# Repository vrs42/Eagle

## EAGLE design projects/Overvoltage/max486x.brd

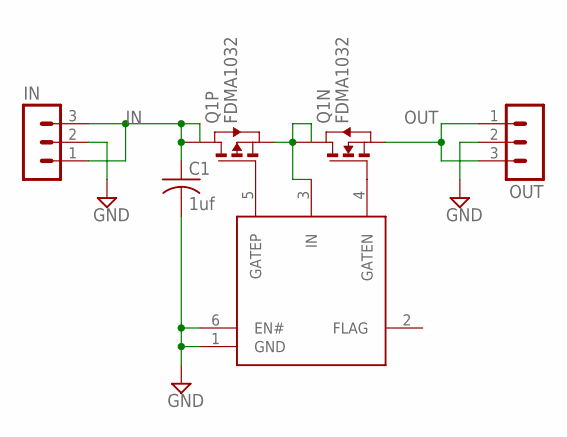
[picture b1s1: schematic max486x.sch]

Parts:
C1: 1uf; C1206
IC1: MAX486X; L622
IN: MA03-1
OUT: MA03-1
Q1: FDMA1032; MLP06

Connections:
GND: C1.2, IC1.1 (GND), IC1.6 (EN#), IN.2, OUT.2
IN: C1.1, IN.1, IN.3, Q1.3 (D1), Q1.3@1 (D)
unnamed: IC1.3 (IN), Q1.4 (S), Q1.6 (D), Q1.6@1 (D1)
unnamed: IC1.5 (GATEP), Q1.5 (G)
unnamed: IC1.4 (GATEN), Q1.2 (G)
OUT: OUT.1, OUT.3, Q1.1 (S)

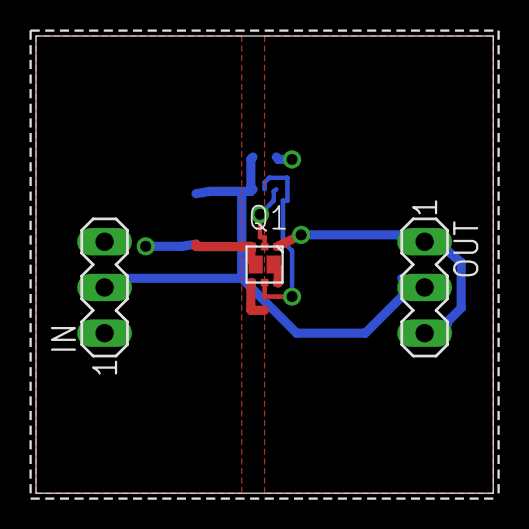
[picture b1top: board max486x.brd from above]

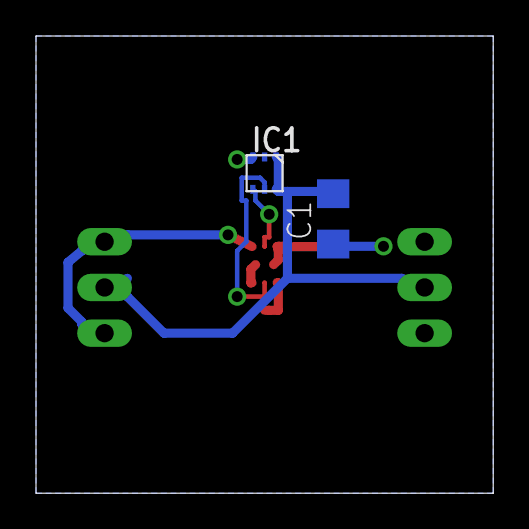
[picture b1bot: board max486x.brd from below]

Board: 2 copper layers, 25.4 x 25.4 mm, 5 parts (2 on the bottom side), 6 nets.

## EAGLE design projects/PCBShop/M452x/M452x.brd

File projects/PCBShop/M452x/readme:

PCBpro Order# 8471
12/01/03
Vincent Slyngstad
P/N M452x Rev A

Please build a quantity of 30 pieces of this 6-layer board. We are requesting 1-oz. finished copper weight, 0.062" thick on FR4 material, green solder mask, and white legend.

The Gerber files included in this zip:

File Name Description:
m452x.cmp Layer 1 (component side) 
m452x.sol Layer 2 solder side
m452x.stc Component-side solder mask
m452x.sts Solder-side solder mask
m452x.plc Component-side silkscreen (nomenclature)
m452x.drd Excellon drill file
m452x.drl Drill tool description 

Any technical questions can be referred to v.slyngstad@verizon.net. 
My contact number is 503-259-9615.

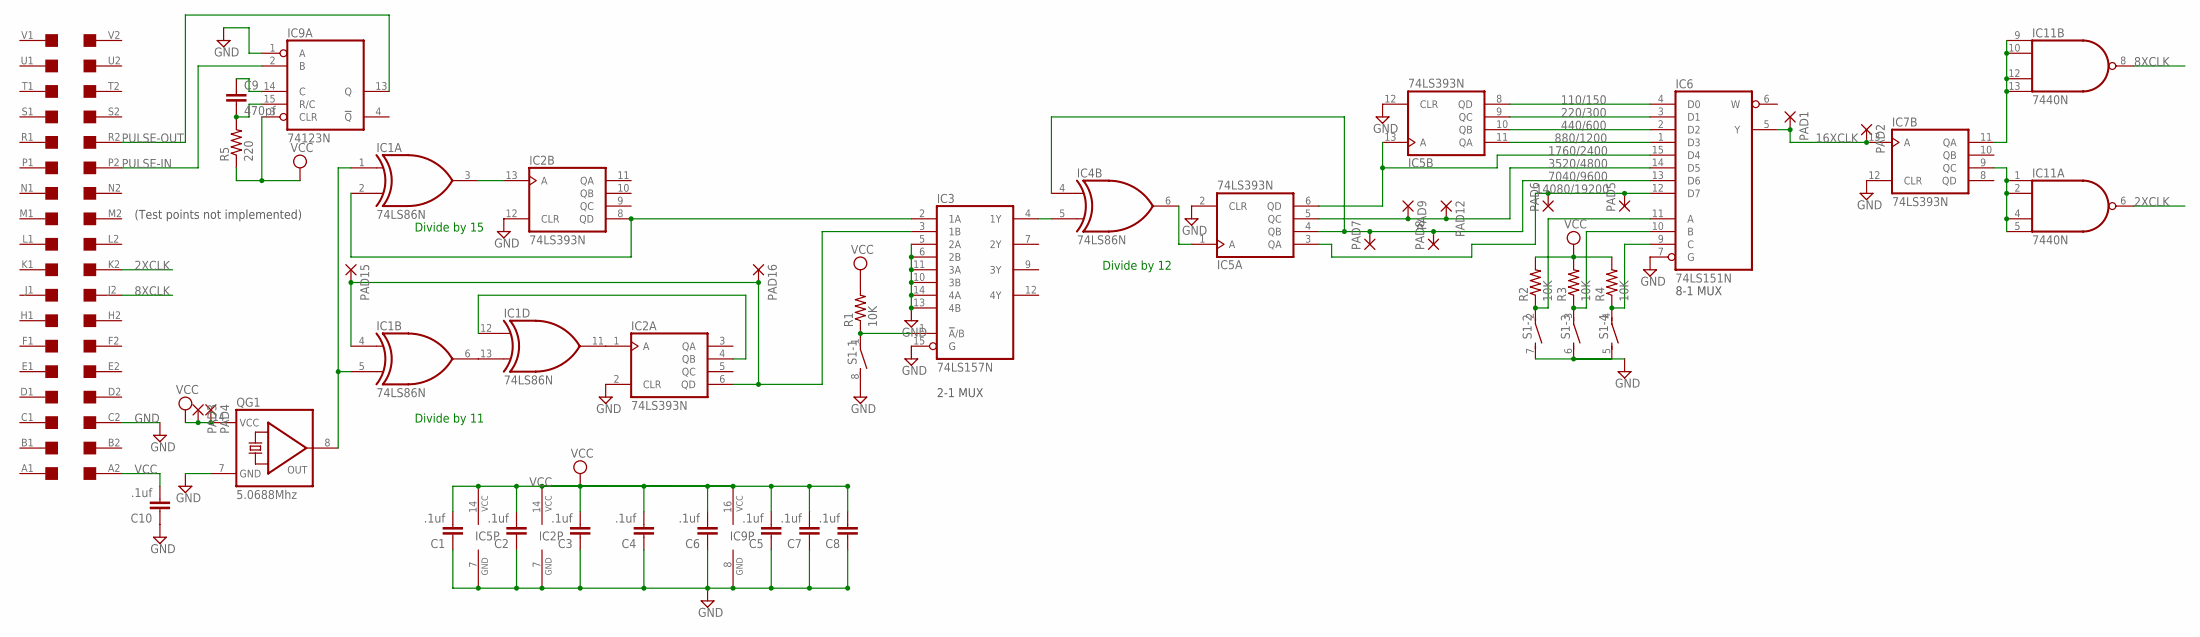
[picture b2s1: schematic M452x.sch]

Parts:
C1, C2, C3, C4, C5, C6, C7, C8, C10: .1uf; C050-025X075
C9: 470pf; C050-025X075
IC1, IC4: 74LS86N; DIL14
IC2, IC5, IC7: 74LS393N; DIL14
IC3: 74LS157N; DIL16
IC6: 74LS151N; DIL16
IC9: 74123N; DIL16
IC11: 7440N; DIL14
PAD1, PAD2, PAD3, PAD4, PAD5, PAD6, PAD7, PAD8, PAD9, PAD12, PAD15, PAD16: 1,6/0,8
QG1: 5.0688Mhz; DIL14S
R1, R2, R3, R4: 10K; 0204/7
R5: 220; 0204/7
S1: DIP04S
U$1: DEC-FLIPCHIP

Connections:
2XCLK: IC11.6 (O), U$1.K2
8XCLK: IC11.8 (O), U$1.J2
16XCLK: IC6.5 (Y), IC7.13 (A), PAD1.1, PAD2.1
110/150: IC5.8 (QD), IC6.4 (D0)
220/300: IC5.9 (QC), IC6.3 (D1)
440/600: IC5.10 (QB), IC6.2 (D2)
880/1200: IC5.11 (QA), IC6.1 (D3)
1760/2400: IC5.6 (QD), IC5.13 (A), IC6.15 (D4)
3520/4800: IC5.5 (QC), IC6.14 (D5), PAD9.1, PAD12.1
7040/9600: IC4.4 (I0), IC5.4 (QB), IC6.13 (D6), PAD7.1, PAD8.1
14080/19200: IC5.3 (QA), IC6.12 (D7), PAD5.1, PAD6.1
GND: C1.1, C2.1, C3.1, C4.1, C5.1, C6.1, C7.1, C8.1, C10.1, IC1.7 (GND), IC2.2 (CLR), IC2.7 (GND), IC2.12 (CLR), IC3.5 (2A), IC3.6 (2B), IC3.8 (GND), IC3.10 (3B), IC3.11 (3A), IC3.13 (4B), IC3.14 (4A), IC3.15 (G), IC4.7 (GND), IC5.2 (CLR), IC5.7 (GND), IC5.12 (CLR), IC6.7 (G), IC6.8 (GND), IC7.7 (GND), IC7.12 (CLR), IC9.1 (A), IC9.8 (GND), IC11.7 (GND), QG1.7 (GND), S1.5 (2), S1.6 (2), S1.7 (2), S1.8 (2), U$1.C2
unnamed: IC1.1 (I0), IC1.5 (I1), QG1.8 (OUT)
unnamed: IC1.2 (I1), IC2.8 (QD), IC3.2 (1A)
unnamed: IC1.4 (I0), IC2.6 (QD), IC3.3 (1B), PAD15.1, PAD16.1
unnamed: IC1.3 (O), IC2.13 (A)
unnamed: IC1.11 (O), IC2.1 (A)
unnamed: IC6.11 (A), R2.1, S1.2 (1)
unnamed: IC3.4 (1Y), IC4.5 (I1)
unnamed: IC7.9 (QC), IC11.1 (I0), IC11.2 (I1), IC11.4 (I2), IC11.5 (I3)
unnamed: IC4.6 (O), IC5.1 (A)
unnamed: IC7.11 (QA), IC11.9 (I0), IC11.10 (I1), IC11.12 (I2), IC11.13 (I3)
unnamed: IC6.10 (B), R3.1, S1.3 (1)
unnamed: IC6.9 (C), R4.1, S1.4 (1)
unnamed: IC1.6 (O), IC1.13 (I1)
unnamed: IC3.1 (!A!/B), R1.1, S1.1
unnamed: IC1.12 (I0), IC2.4 (QB)
unnamed: C9.2, IC9.15 (R/C), R5.2
unnamed: C9.1, IC9.14 (C)
PULSE-IN: IC9.2 (B), U$1.P2
PULSE-OUT: IC9.13 (Q), U$1.R2
VCC: C1.2, C2.2, C3.2, C4.2, C5.2, C6.2, C7.2, C8.2, C10.2, IC1.14 (VCC), IC2.14 (VCC), IC3.16 (VCC), IC4.14 (VCC), IC5.14 (VCC), IC6.16 (VCC), IC7.14 (VCC), IC9.3 (CLR), IC9.16 (VCC), IC11.14 (VCC), PAD3.1, PAD4.1, QG1.14 (VCC), R1.2, R2.2, R3.2, R4.2, R5.1, U$1.A2

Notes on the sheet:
Divide by 11
Divide by 15
Divide by 12
(Test points not implemented)
2-1 MUX
8-1 MUX

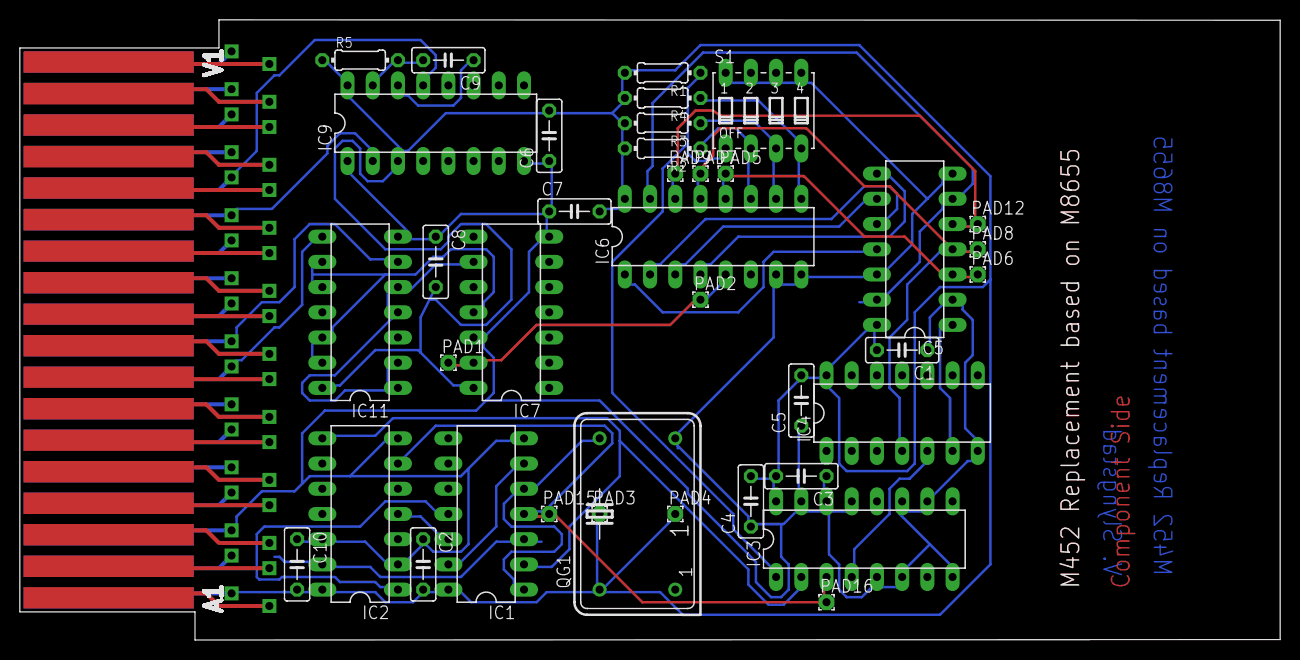
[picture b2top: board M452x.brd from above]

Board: 2 copper layers, 127.0 x 62.5 mm, 39 parts (0 on the bottom side), 32 nets.

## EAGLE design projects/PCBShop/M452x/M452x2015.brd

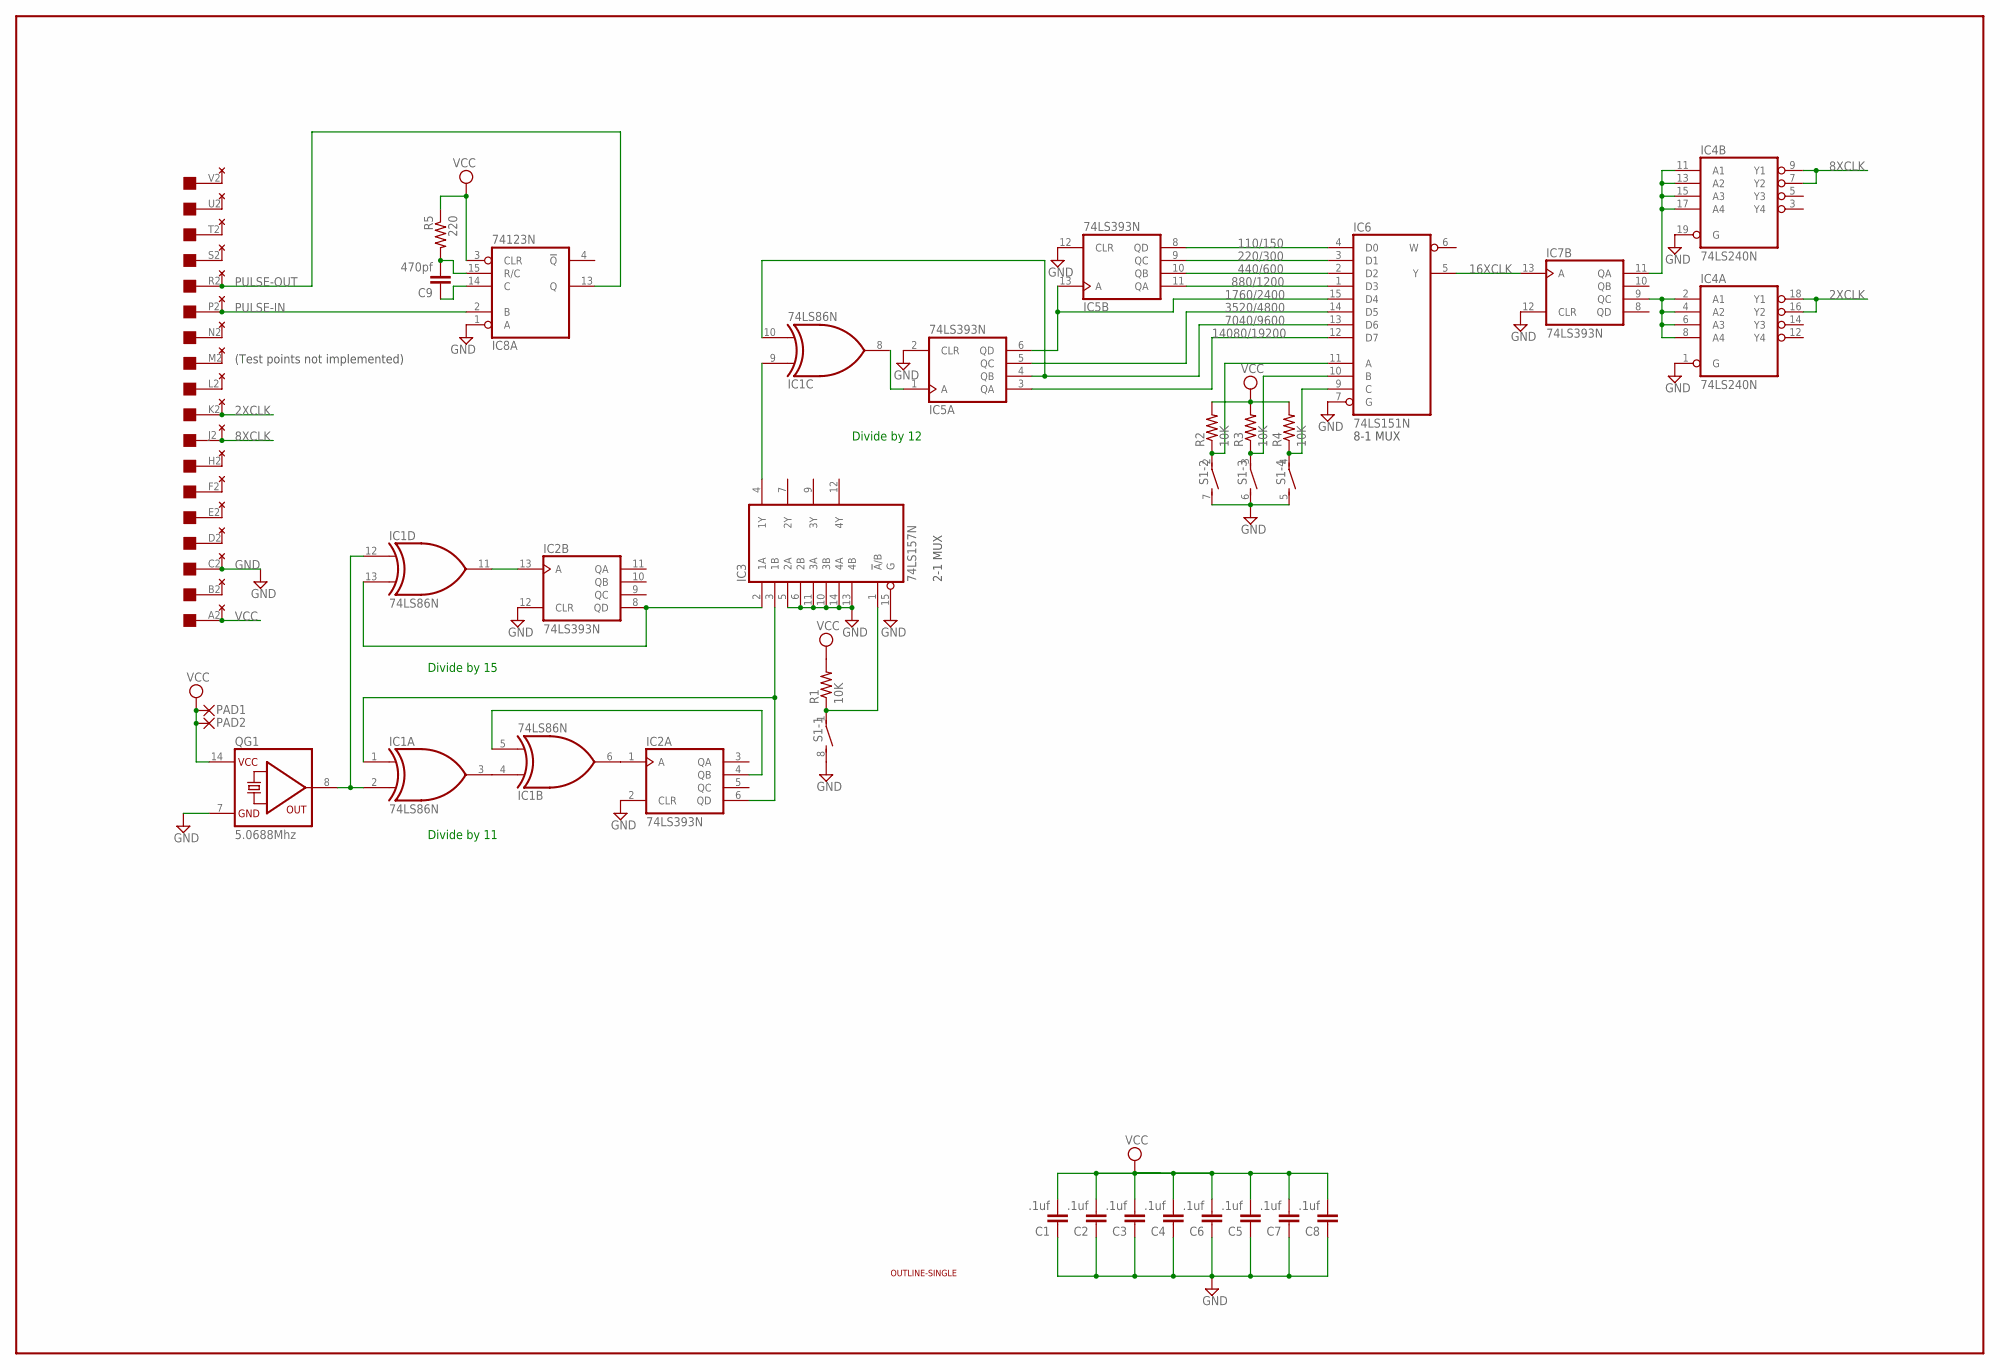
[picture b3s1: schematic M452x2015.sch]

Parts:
C1, C2, C3, C4, C5, C6, C7, C8: .1uf; C050-025X075
C9: 470pf; C050-025X075
IC1: 74LS86N; DIL14
IC2, IC5, IC7: 74LS393N; DIL14
IC3: 74LS157N; DIL16
IC4: 74LS240N; DIL20
IC6: 74LS151N; DIL16
IC8: 74123N; DIL16
PAD1, PAD2: 1,6/0,8
QG1: 5.0688Mhz; DIL14S
R1, R2, R3, R4: 10K; 0204/7
R5: 220; 0204/7
S1: DIP04S
U$1: OUTLINE-SINGLE; SINGLE
U$2: EDGE-1; EDGE-CON1
U$3: THRU-HOLE1

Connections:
2XCLK: IC4.16 (Y2), IC4.18 (Y1), U$2.K2, U$3.K2
8XCLK: IC4.7 (Y2), IC4.9 (Y1), U$2.J2, U$3.J2
16XCLK: IC6.5 (Y), IC7.13 (A)
110/150: IC5.8 (QD), IC6.4 (D0)
220/300: IC5.9 (QC), IC6.3 (D1)
440/600: IC5.10 (QB), IC6.2 (D2)
880/1200: IC5.11 (QA), IC6.1 (D3)
1760/2400: IC5.6 (QD), IC5.13 (A), IC6.15 (D4)
3520/4800: IC5.5 (QC), IC6.14 (D5)
7040/9600: IC1.10 (I1), IC5.4 (QB), IC6.13 (D6)
14080/19200: IC5.3 (QA), IC6.12 (D7)
GND: C1.1, C2.1, C3.1, C4.1, C5.1, C6.1, C7.1, C8.1, IC1.7 (GND), IC2.2 (CLR), IC2.7 (GND), IC2.12 (CLR), IC3.5 (2A), IC3.6 (2B), IC3.8 (GND), IC3.10 (3B), IC3.11 (3A), IC3.13 (4B), IC3.14 (4A), IC3.15 (G), IC4.1 (G), IC4.10 (GND), IC4.19 (G), IC5.2 (CLR), IC5.7 (GND), IC5.12 (CLR), IC6.7 (G), IC6.8 (GND), IC7.7 (GND), IC7.12 (CLR), IC8.1 (A), IC8.8 (GND), QG1.7 (GND), S1.5 (2), S1.6 (2), S1.7 (2), S1.8 (2), U$2.C2, U$3.C2
unnamed: IC1.2 (I1), IC1.12 (I0), QG1.8 (OUT)
unnamed: IC1.13 (I1), IC2.8 (QD), IC3.2 (1A)
unnamed: IC1.1 (I0), IC2.6 (QD), IC3.3 (1B)
unnamed: U$2.H2, U$3.H2
unnamed: U$2.L2, U$3.L2
unnamed: IC1.11 (O), IC2.13 (A)
unnamed: IC1.6 (O), IC2.1 (A)
unnamed: IC6.11 (A), R2.1, S1.2 (1)
unnamed: IC1.9 (I0), IC3.4 (1Y)
unnamed: IC4.2 (A1), IC4.4 (A2), IC4.6 (A3), IC4.8 (A4), IC7.9 (QC)
unnamed: IC1.8 (O), IC5.1 (A)
unnamed: IC4.11 (A1), IC4.13 (A2), IC4.15 (A3), IC4.17 (A4), IC7.11 (QA)
unnamed: IC6.10 (B), R3.1, S1.3 (1)
unnamed: IC6.9 (C), R4.1, S1.4 (1)
unnamed: IC1.3 (O), IC1.4 (I0)
unnamed: U$2.M2, U$3.M2
unnamed: IC3.1 (!A!/B), R1.1, S1.1
unnamed: U$2.N2, U$3.N2
unnamed: IC1.5 (I1), IC2.4 (QB)
unnamed: U$2.F2, U$3.F2
unnamed: C9.2, IC8.15 (R/C), R5.2
unnamed: C9.1, IC8.14 (C)
unnamed: U$2.E2, U$3.E2
unnamed: U$2.D2, U$3.D2
unnamed: U$2.S2, U$3.S2
unnamed: U$2.B2, U$3.B2
unnamed: U$2.T2, U$3.T2
unnamed: U$2.U2, U$3.U2
unnamed: U$2.V2, U$3.V2
PULSE-IN: IC8.2 (B), U$2.P2, U$3.P2
PULSE-OUT: IC8.13 (Q), U$2.R2, U$3.R2
VCC: C1.2, C2.2, C3.2, C4.2, C5.2, C6.2, C7.2, C8.2, IC1.14 (VCC), IC2.14 (VCC), IC3.16 (VCC), IC4.20 (VCC), IC5.14 (VCC), IC6.16 (VCC), IC7.14 (VCC), IC8.3 (CLR), IC8.16 (VCC), PAD1.1, PAD2.1, QG1.14 (VCC), R1.2, R2.2, R3.2, R4.2, R5.1, U$2.A2, U$3.A2

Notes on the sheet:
Divide by 11
Divide by 15
Divide by 12
(Test points not implemented)
2-1 MUX
8-1 MUX

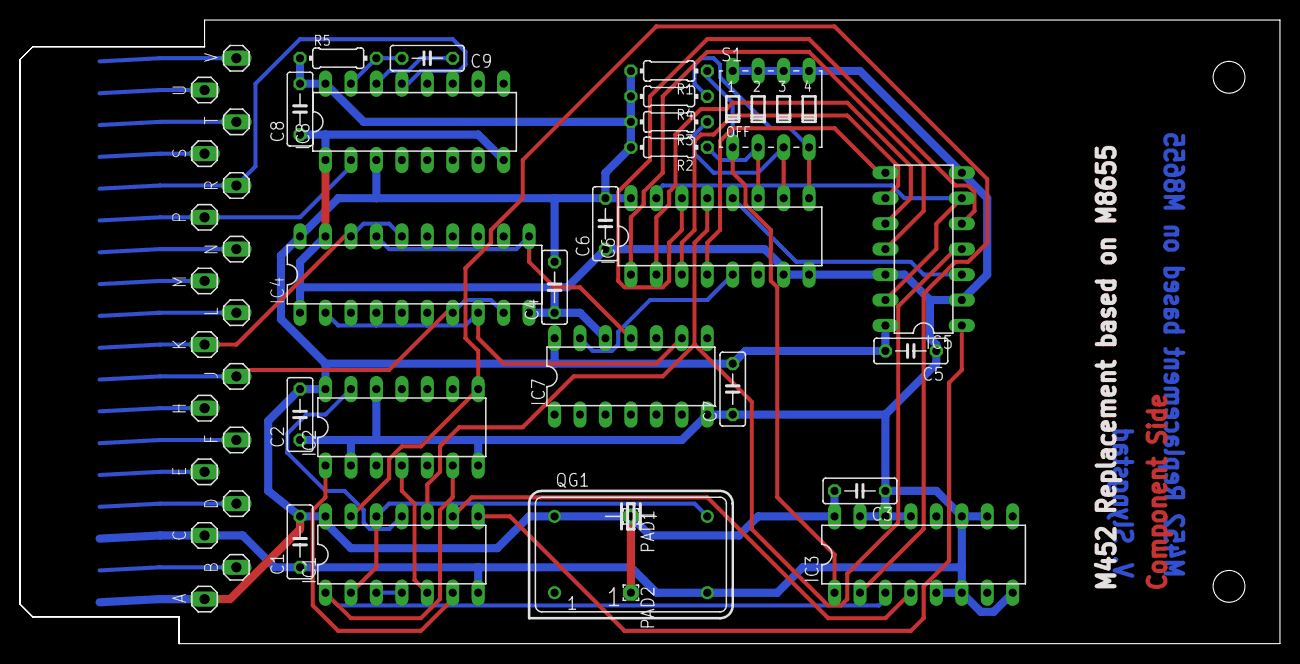
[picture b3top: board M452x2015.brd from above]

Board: 2 copper layers, 125.7 x 62.2 mm, 29 parts (0 on the bottom side), 44 nets.

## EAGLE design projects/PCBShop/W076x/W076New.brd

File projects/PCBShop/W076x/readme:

PCBpro Order# 8500
12/01/03
Vincent Slyngstad
P/N W076o Rev A

Please build a quantity of 30 pieces of this 6-layer board. We are requesting 1-oz. finished copper weight, 0.062" thick on FR4 material, green solder mask, and white legend.

The Gerber files included in this zip:

File Name Description:
w076o.cmp Layer 1 (component side) 
w076o.sol Layer 2 solder side
w076o.stc Component-side solder mask
w076o.sts Solder-side solder mask
w076o.plc Component-side silkscreen (nomenclature)
w076o.drd Excellon drill file
w076o.drl Drill tool description 

Any technical questions can be referred to v.slyngstad@verizon.net. 
My contact number is 503-259-9615.

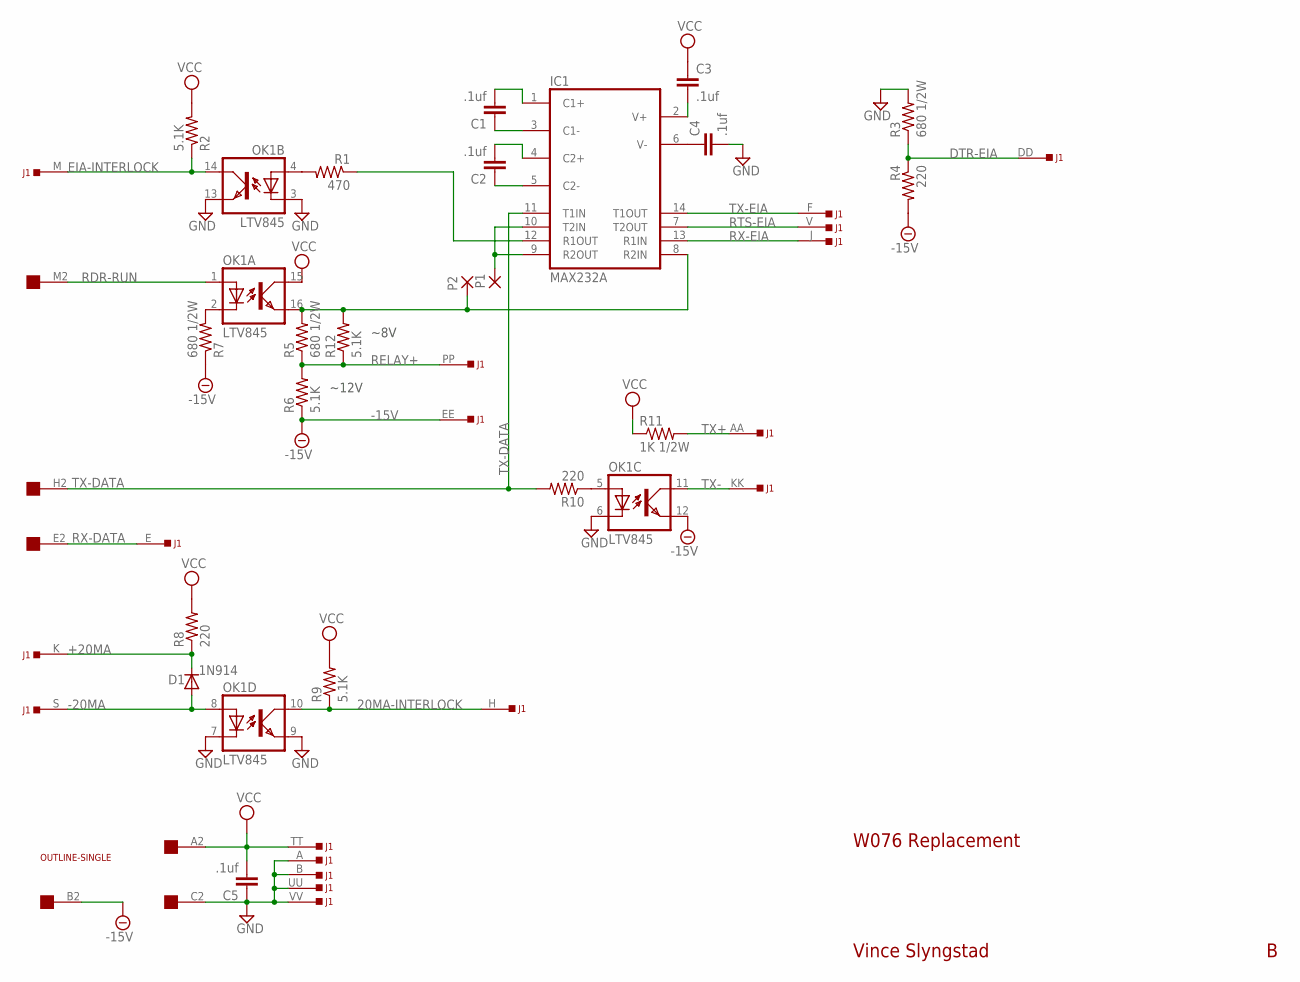
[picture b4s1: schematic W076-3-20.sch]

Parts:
C1, C2, C3, C4, C5: .1uf; C050-025X075
D1: 1N914; DO41-10
IC1: MAX232A; DIL16
J1: DEC40PINSH; DEC40PINH
OK1: LTV845; DIL16
P1, P2: 1,6/0,8
R1: 470; 0207/10
R2, R6, R9, R12: 5.1K; 0207/10
R3, R5, R7: 680 1/2W; 0207/12
R4, R8, R10: 220; 0207/10
R11: 1K 1/2W; 0207/10
U$2: EDGE-1; EDGE-CON1
U$3: OUTLINE-SINGLE; SINGLE

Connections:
20MA-INTERLOCK: J1.H, OK1.10 (COL), R9.1
+20MA: D1.C, J1.K, R8.1
-20MA: D1.A, J1.S, OK1.8 (A)
DTR-EIA: J1.DD, R3.1, R4.1
EIA-INTERLOCK: J1.M, OK1.14 (COL), R2.1
unnamed: C2.1, IC1.5 (C2-)
unnamed: C2.2, IC1.4 (C2+)
unnamed: C1.2, IC1.1 (C1+)
unnamed: C1.1, IC1.3 (C1-)
unnamed: OK1.2 (C), R7.2
unnamed: IC1.9 (R2OUT), IC1.10 (T2IN), P1.1
unnamed: IC1.8 (R2IN), OK1.16 (EMIT), P2.1, R5.2, R12.2
unnamed: IC1.12 (R1OUT), R1.1
unnamed: C3.2, IC1.2 (V+)
unnamed: C4.1, IC1.6 (V-)
unnamed: OK1.4 (A), R1.2
unnamed: OK1.5 (A), R10.1
RDR-RUN: OK1.1 (A), U$2.M2
RELAY+: J1.PP, R5.1, R6.2, R12.1
RTS-EIA: IC1.7 (T2OUT), J1.V
RX-DATA: J1.E, U$2.E2
RX-EIA: IC1.13 (R1IN), J1.J
TX+: J1.AA, R11.2
TX-: J1.KK, OK1.11 (COL)
TX-DATA: IC1.11 (T1IN), R10.2, U$2.H2
TX-EIA: IC1.14 (T1OUT), J1.F
VCC: C3.1, C5.2, IC1.16 (VCC), J1.TT, OK1.15 (COL), R2.2, R8.2, R9.2, R11.1, U$2.A2

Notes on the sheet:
W076 Replacement
Vince Slyngstad
~8V
~12V

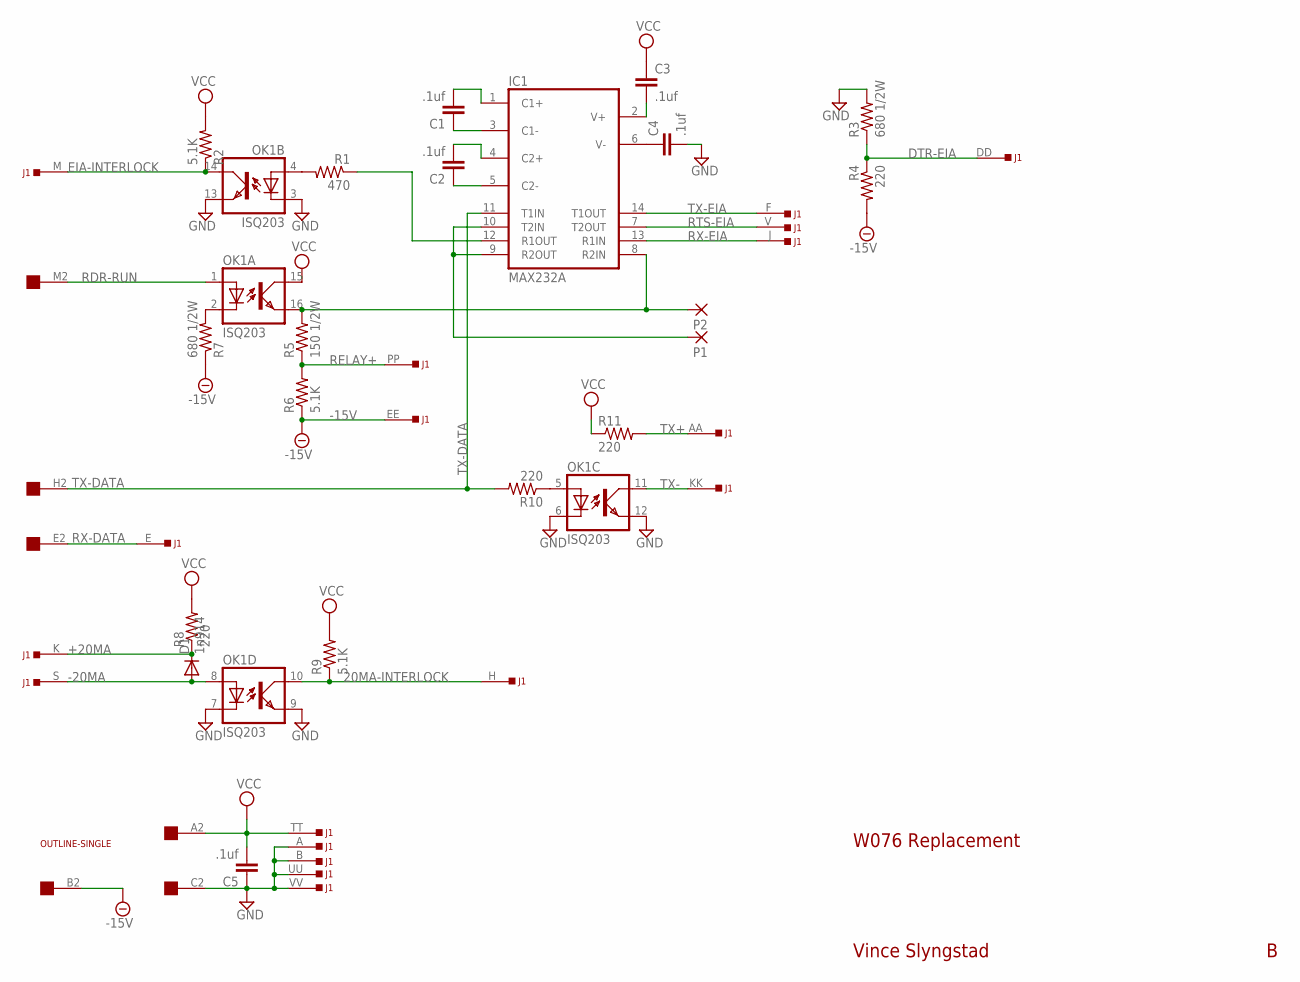
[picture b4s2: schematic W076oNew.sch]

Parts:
C1, C2, C3, C4, C5: .1uf; C050-025X075
D1: 1n914; DO41-10
IC1: MAX232A; DIL16
J1: DEC40PINSH; DEC40PINH
OK1: ISQ203; DIL16
P1, P2: 1,6/0,8
R1: 470; 0207/10
R2, R6, R9: 5.1K; 0207/10
R3, R7: 680 1/2W; 0207/12
R4, R8, R10, R11: 220; 0207/10
R5: 150 1/2W; 0207/12
U$2: EDGE-1; EDGE-CON1
U$3: OUTLINE-SINGLE; SINGLE

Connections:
20MA-INTERLOCK: J1.H, OK1.10 (COL), R9.1
+20MA: D1.C, J1.K, R8.1
-20MA: D1.A, J1.S, OK1.8 (A)
DTR-EIA: J1.DD, R3.1, R4.1
EIA-INTERLOCK: J1.M, OK1.14 (COL), R2.1
unnamed: C2.1, IC1.5 (C2-)
unnamed: C2.2, IC1.4 (C2+)
unnamed: C1.2, IC1.1 (C1+)
unnamed: C1.1, IC1.3 (C1-)
unnamed: OK1.2 (C), R7.2
unnamed: IC1.9 (R2OUT), IC1.10 (T2IN), P1.1
unnamed 11: IC1.8 (R2IN), OK1.16 (EMIT), P2.1, R5.2; also elsewhere on the board
unnamed: IC1.12 (R1OUT), R1.1
unnamed: C3.2, IC1.2 (V+)
unnamed: C4.1, IC1.6 (V-)
unnamed: OK1.4 (A), R1.2
unnamed: OK1.5 (A), R10.1
RDR-RUN: OK1.1 (A), U$2.M2
RELAY+: J1.PP, R5.1, R6.2; also elsewhere on the board
RTS-EIA: IC1.7 (T2OUT), J1.V
RX-DATA: J1.E, U$2.E2
RX-EIA: IC1.13 (R1IN), J1.J
TX+: J1.AA, R11.2
TX-: J1.KK, OK1.11 (COL)
TX-DATA: IC1.11 (T1IN), R10.2, U$2.H2
TX-EIA: IC1.14 (T1OUT), J1.F
VCC: C3.1, C5.2, IC1.16 (VCC), J1.TT, OK1.15 (COL), R2.2, R8.2, R9.2, R11.1, U$2.A2

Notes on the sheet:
W076 Replacement
Vince Slyngstad

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
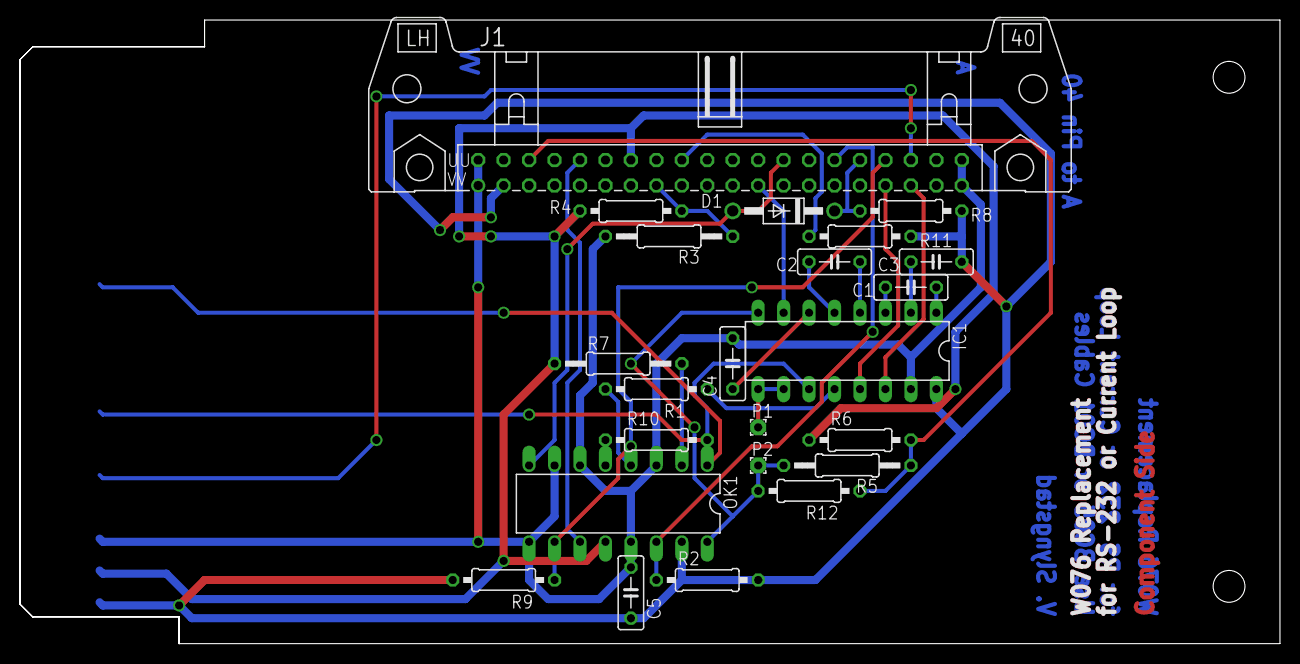
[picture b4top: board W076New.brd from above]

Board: 2 copper layers, 125.7 x 62.2 mm, 25 parts (0 on the bottom side), 29 nets.

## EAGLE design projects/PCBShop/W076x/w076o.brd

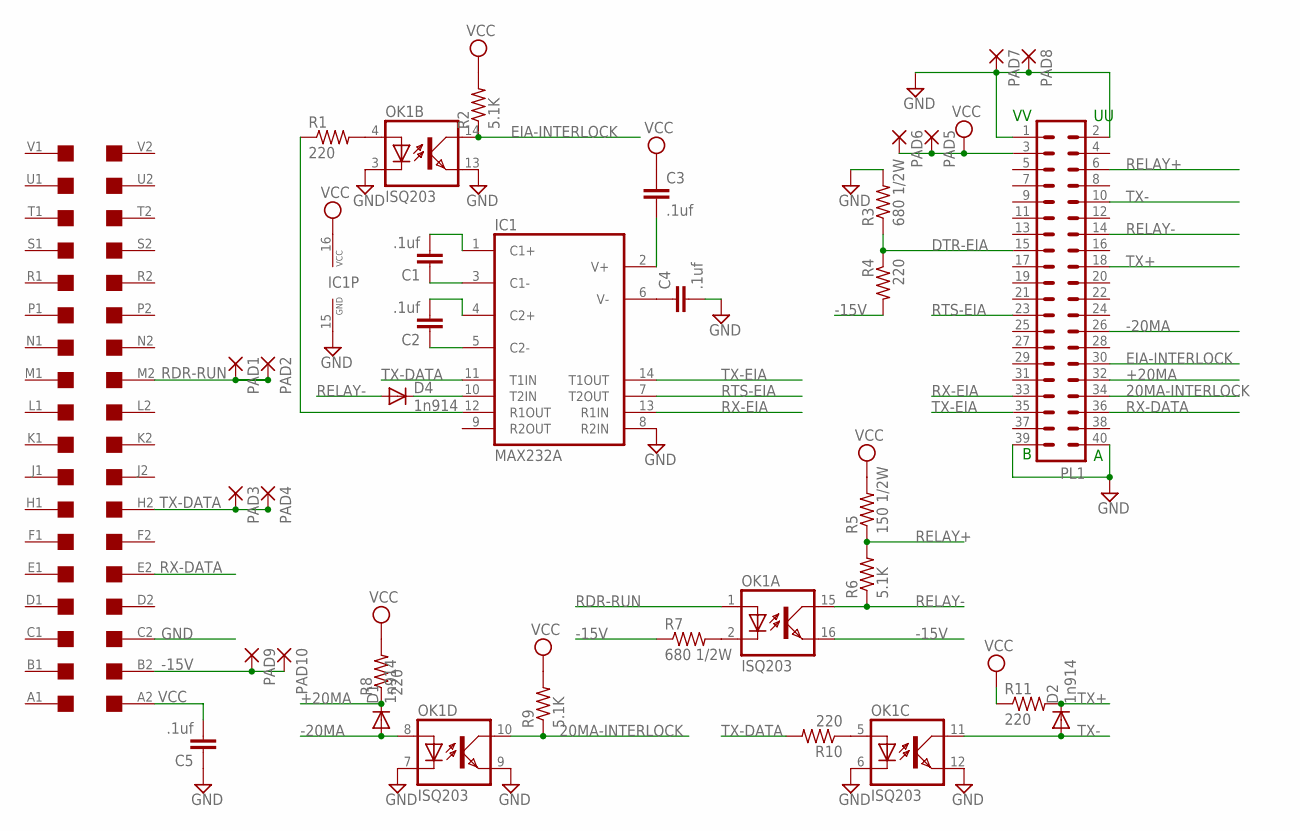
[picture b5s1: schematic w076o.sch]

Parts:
C1, C2, C3, C4, C5: .1uf; C050-025X075
D1, D2, D4: 1n914; DO41-10
IC1: MAX232A; DIL16
OK1: ISQ203; DIL16
PAD1, PAD2, PAD3, PAD4, PAD5, PAD6, PAD7, PAD8, PAD9, PAD10: 1,6/0,8
PL1: 40H
R1, R4, R8, R10, R11: 220; 0207/10
R2, R6, R9: 5.1K; 0207/10
R3, R7: 680 1/2W; 0207/12
R5: 150 1/2W; 0207/12
U$1: DEC-FLIPCHIP

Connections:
20MA-INTERLOCK: OK1.10 (COL), PL1.34, R9.1
+20MA: D1.C, PL1.32, R8.1
-15V: OK1.16 (EMIT), PAD9.1, PAD10.1, R4.2, R7.1, U$1.B2
-20MA: D1.A, OK1.8 (A), PL1.26
DTR-EIA: PL1.15, R3.1, R4.1
EIA-INTERLOCK: OK1.14 (COL), PL1.30, R2.1
GND: C4.2, C5.1, IC1.8 (R2IN), IC1.15 (GND), OK1.3 (C), OK1.6 (C), OK1.7 (C), OK1.9 (EMIT), OK1.12 (EMIT), OK1.13 (EMIT), PAD7.1, PAD8.1, PL1.1, PL1.2, PL1.39, PL1.40, R3.2, U$1.C2
unnamed: C2.1, IC1.5 (C2-)
unnamed: C2.2, IC1.4 (C2+)
unnamed: C1.2, IC1.1 (C1+)
unnamed: C1.1, IC1.3 (C1-)
unnamed: OK1.2 (C), R7.2
unnamed: D4.C, IC1.10 (T2IN)
unnamed: IC1.12 (R1OUT), R1.1
unnamed: C3.2, IC1.2 (V+)
unnamed: C4.1, IC1.6 (V-)
unnamed: OK1.4 (A), R1.2
unnamed: OK1.5 (A), R10.1
RDR-RUN: OK1.1 (A), PAD1.1, PAD2.1, U$1.M2
RELAY+: PL1.6, R5.1, R6.2
RELAY-: D4.A, OK1.15 (COL), PL1.14, R6.1
RTS-EIA: IC1.7 (T2OUT), PL1.23
RX-DATA: PL1.36, U$1.E2
RX-EIA: IC1.13 (R1IN), PL1.33
TX+: D2.C, PL1.18, R11.2
TX-: D2.A, OK1.11 (COL), PL1.10
TX-DATA: IC1.11 (T1IN), PAD3.1, PAD4.1, R10.2, U$1.H2
TX-EIA: IC1.14 (T1OUT), PL1.35
VCC: C3.1, C5.2, IC1.16 (VCC), PAD5.1, PAD6.1, PL1.3, R2.2, R5.2, R8.2, R9.2, R11.1, U$1.A2

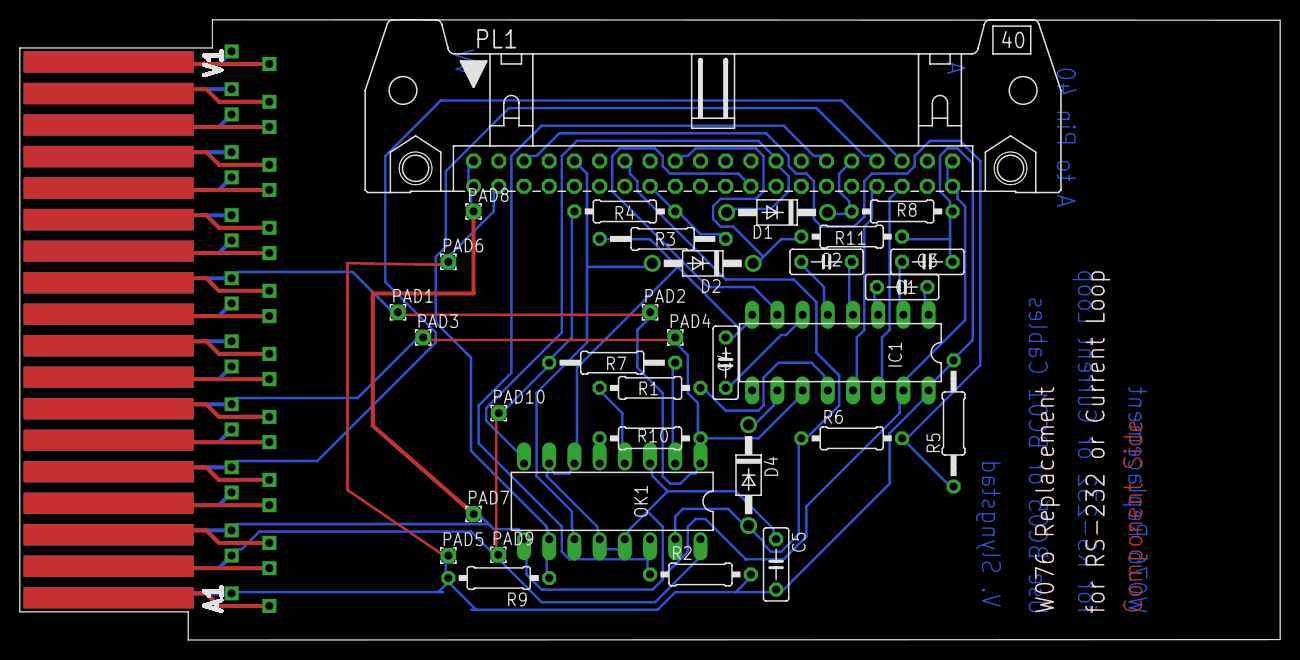
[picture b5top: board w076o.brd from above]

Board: 2 copper layers, 127.0 x 62.5 mm, 33 parts (0 on the bottom side), 29 nets.
